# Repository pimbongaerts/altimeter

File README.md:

# Altimeter_v2

Intervalometer with serial interface based on Mega2560 MCU

*Current application:*

* Intervalometer for photogrammetry surveys (triggering a Canon 5DsR DSLR every second)
* Real-time sensor feedback underwater (through attached OLED display):
  * Levelling and altitude (through 2 x altimeters: [BlueRobotics Ping Sonar](https://bluerobotics.com/store/sensors-sonars-cameras/sonar/ping-sonar-r2-rp/))
  * Read-out USBL communications (through [BluePrint Subsea X150 USBL](https://www.blueprintsubsea.com/pages/product.php?PN=BP00795))
  * Depth and "bottom-depth" based on altitude (through [BlueRobotics Depth Sensor](https://bluerobotics.com/store/sensors-sonars-cameras/sensors/bar30-sensor-r1/))
  * Stopwatch & intervalometer count (triggered by Remora remote)
* Logging synchronized sensor data on SD card

*Features:*

* Real-time clock (RTC) for timekeeping
* SD-card reader to log sensor data
* 4-Channel Optocoupler to trigger camera(s)
* Step-down regulator to run board & DSLR camera off external battery (e.g. from dive propulsion vehicle)
* Supports I2C (3.3V or 5V logic), UART and RS232 sensors
* Connectors for remote controller & I2C or SPI display
* Headers to connect with [Robotdyn MCU-PRO Mega 2560 board](https://robotdyn.com/mcu-pro-mega-2560-atmega2560-16au-usb-ch340c-with-pinheaders-2-lines-pinheaders-pitch-0-1.html), which can be programmed using Arduino IDE
* Fits inside [BlueRobotics 2" watertight enclosure](https://bluerobotics.com/product-category/watertight-enclosures/) (see image below)

## Schematic

[PDF Schematic](altimeter_v2_schematic.pdf)

* Note: LP3966 on schematic replaced with [TL1963AKTTRG3](https://www.digikey.com/product-detail/en/texas-instruments/TL1963AKTTRG3/296-35958-1-ND/4135050) (has the same footprint)

## Arduino code

[Arduino code](altimeter_v2.ino) (some features are currently commented out)

## PCB Design

[KiCad PCB file](altimeter_v2.kicad_pcb) / [Bill of materials](altimeter_v2_bill.csv)

* Note: footprint of the [XC1195CT-ND Crystal](https://www.digikey.com/product-detail/en/ecs-inc/ECS-327-12-5-17X-TR/XC1195CT-ND/827659) turned out to be incorrect, but could easily remedied with direct bridge to RTC pin

## Underwater housing

Image shows board installed in a [BlueRobotics 2" watertight enclosure](https://bluerobotics.com/product-category/watertight-enclosures/), and with a 20x4 OLED display connected. On the left side, there are penetrators for an on/off switch, a [BlueRobotics Depth Sensor](https://bluerobotics.com/store/sensors-sonars-cameras/sensors/bar30-sensor-r1/), and 2 x [BlueRobotics Ping Sonar](https://bluerobotics.com/store/sensors-sonars-cameras/sonar/ping-sonar-r2-rp/) (although on the photo only one connected, hence the "error" on the top-right of the display). On the right side, there is an Ikelite connector to connect with the camera (power and trigger), another Ikelite connector for the 3-button remote (Remora), a penetrator for a cable connecting with the Dive-Xtras Piranha DPV battery, and a penetrator for the cable connecting with the [BluePrint Subsea X150 USBL](https://www.blueprintsubsea.com/pages/product.php?PN=BP00795).

## Final notes

Acknowledging John Atkins for all the design advice! Currently working on next iteration with SAMD51 integrated on the board (no external controller board required).

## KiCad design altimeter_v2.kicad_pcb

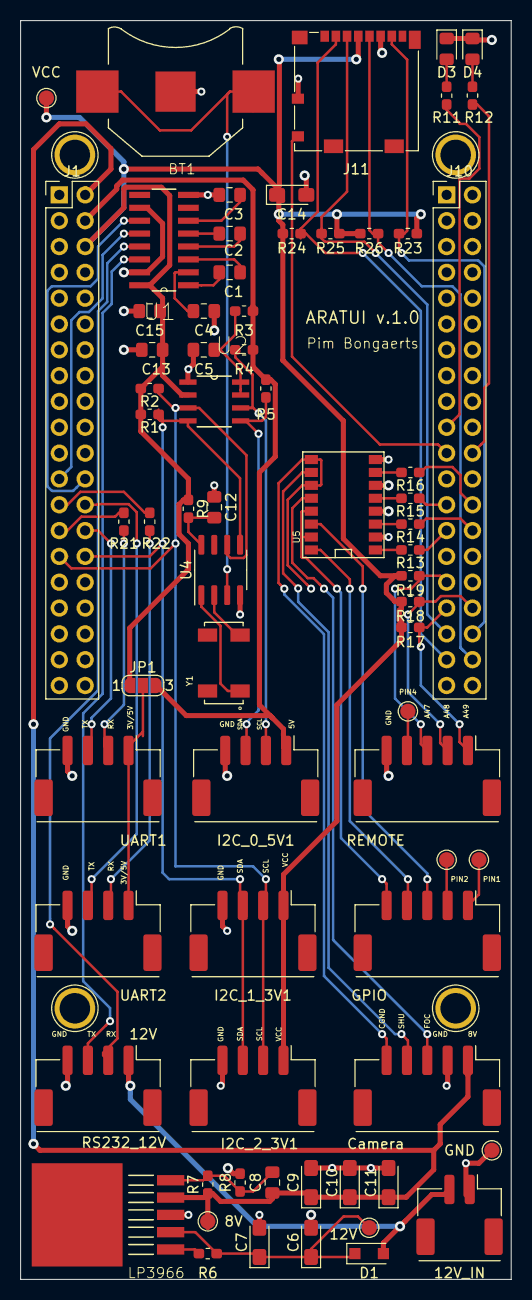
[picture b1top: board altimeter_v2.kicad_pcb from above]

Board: 2 copper layers, 48.3 x 123.8 mm, 70 parts (0 on the bottom side), 63 nets.

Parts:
8V, 12V: TestPoint; TestPoint_Pad_D1.5mm
12V_IN: 12V_IN; Molex_CLIK-Mate_502443-0270_1x02-1MP_P2.00mm_Vertical
BT1: BK-885; BAT_BK-885
C1, C2, C3, C4, C5, C12, C13, C15: 1uF; C_0805_2012Metric_Pad1.15x1.40mm_HandSolder
C6, C7, C9, C10, C11, C14: 33uF; CP_EIA-3216-10_Kemet-I_Pad1.58x1.35mm_HandSolder
C8: 68pF; C_0805_2012Metric_Pad1.15x1.40mm_HandSolder
Camera: Camera; Molex_CLIK-Mate_502443-0570_1x05-1MP_P2.00mm_Vertical
D1: D; D_SOD-123F
D3, D4: LED_Small; LED_0805_2012Metric_Pad1.15x1.40mm_HandSolder
GND: TestPoint; TestPoint_Pad_D1.5mm
GPIO: GPIO; Molex_CLIK-Mate_502443-0570_1x05-1MP_P2.00mm_Vertical
I2C_0_5V1: I2C_0_5V; Molex_CLIK-Mate_502443-0470_1x04-1MP_P2.00mm_Vertical
I2C_1_3V1: I2C_1_3V; Molex_CLIK-Mate_502443-0470_1x04-1MP_P2.00mm_Vertical
I2C_2_3V1: I2C_2_3V; Molex_CLIK-Mate_502443-0470_1x04-1MP_P2.00mm_Vertical
J1, J10: Conn_02x20_Odd_Even; PinHeader_2x20_P2.54mm_Vertical
J11: 5025700893; microSD_HC_Molex_104031-0811
JP1: SJ_Supply; SolderJumper-3_P1.3mm_Open_RoundedPad1.0x1.5mm_NumberLabels
LP3966: LP3966-ADJ_8.4V; TO170P1435X457-5N
PIN1, PIN2, PIN4: TestPoint; TestPoint_Pad_D1.5mm
R1, R2, R4, R5: 1.1K; R_0603_1608Metric_Pad1.05x0.95mm_HandSolder
R3: 200K; R_0603_1608Metric_Pad1.05x0.95mm_HandSolder
R6, R8, R9, R17, R18, R19, R21, R22, R23, R24, R25, R26: 11K; R_0603_1608Metric_Pad1.05x0.95mm_HandSolder
R7: 69K; R_0603_1608Metric_Pad1.05x0.95mm_HandSolder
R11, R12, R13, R14, R15, R16: 300; R_0603_1608Metric_Pad1.05x0.95mm_HandSolder
REMOTE: Remote; Molex_CLIK-Mate_502443-0570_1x05-1MP_P2.00mm_Vertical
RS232_12V: RS232; Molex_CLIK-Mate_502443-0470_1x04-1MP_P2.00mm_Vertical
U1: MAX3232CDR; SOIC127P600X175-16N
U2: PCA9306D; SOIC127P600X175-8N
U4: PCF8523T; SOIC-8_3.9x4.9mm_P1.27mm
U5: TCMT4100; SOP-16
UART1: UART_1; Molex_CLIK-Mate_502443-0470_1x04-1MP_P2.00mm_Vertical
UART2: UART_2; Molex_CLIK-Mate_502443-0470_1x04-1MP_P2.00mm_Vertical
VCC: TestPoint; TestPoint_Pad_D1.5mm
Y1: Crystal_Small; XTAL_ECS-.327-12.5-17X-TR

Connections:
+5V: I2C_0_5V1.1, J1.4, JP1.3, R3.1, R4.1, R5.1
+12V: 12V_IN.2, D1.2, RS232_12V.1
ARD35: J10.19, R11.2
ARD36: J10.22, R12.2
ARD37: J10.21, J11.10
ARD40: J10.26, R16.2
ARD41: J10.25, R15.2
ARD42: J10.28, R14.2
ARD43: J10.27, R13.2
ARD47: J10.31, R19.1, REMOTE.3
ARD48: J10.34, R18.1, REMOTE.2
ARD49: J10.33, R17.1, REMOTE.1
GND: 12V_IN.1, BT1.-, C3.1, C4.2, C5.2, C6.2, C7.2, C9.2, C10.2, C11.2, C12.1, C13.1, C14.2, C15.2, Camera.2, D3.1, D4.1, GND.1, I2C_0_5V1.4, I2C_1_3V1.4, I2C_2_3V1.4, J1.1, J1.7, J10.39, J10.40, J11.6, J11.9, LP3966.3, R8.2, REMOTE.5, RS232_12V.4, U1.8, U1.10, U1.15, U2.1, U4.4, U5.2, U5.4, U5.6, U5.8, UART1.4, UART2.4
MISO: J10.36, J11.7, R23.1
MOSI: J10.35, J11.3, R25.1
unnamed: BT1.S1+, BT1.S2+, U4.3
unnamed: C1.1, U1.1
unnamed: C1.2, U1.3
unnamed: C2.1, U1.4
unnamed: C2.2, U1.5
unnamed: C3.2, U1.6
unnamed: C4.1, U1.2
unnamed: C5.1, R3.2, U2.7, U2.8
unnamed: 12V.1, C6.1, C7.1, D1.1, LP3966.2, R6.2
unnamed: C8.2, LP3966.5, R7.2, R8.1
unnamed: C12.2, R9.2, U4.8
unnamed: Camera.3, U5.12
unnamed: Camera.4, U5.10
unnamed: Camera.5, U5.9, U5.11
unnamed: D3.2, R11.1
unnamed: D4.2, R12.1
unnamed: GPIO.1, PIN1.1
unnamed: GPIO.2, PIN2.1
unnamed: GPIO.3, U5.14
unnamed: GPIO.4, U5.16
unnamed: GPIO.5, U5.13, U5.15
unnamed: I2C_0_5V1.2, R4.2, U2.6
unnamed: I2C_0_5V1.3, R5.2, U2.5
unnamed: JP1.2, UART1.1, UART2.1
unnamed: LP3966.1, R6.1
unnamed: R13.1, U5.1
unnamed: R14.1, U5.3
unnamed: R15.1, U5.5
unnamed: R16.1, U5.7
unnamed: R21.2, UART1.2
unnamed: R22.2, UART2.2
unnamed: PIN4.1, REMOTE.4
unnamed: U4.1, Y1.1
unnamed: U4.2, Y1.2
RXD1: J1.27, R21.1
RXD2: J1.25, R22.1
RXD3: J1.23, U1.12
RX_RS232: RS232_12V.2, U1.13
SCK: J10.38, J11.5, R26.1
SCL: I2C_1_3V1.2, I2C_2_3V1.2, J1.29, R2.2, U2.3, U4.6
SDA: I2C_1_3V1.3, I2C_2_3V1.3, J1.30, R1.2, U2.4, U4.5
SS: J10.37, J11.2, R24.1
TXD1: J1.28, UART1.3
TXD2: J1.26, UART2.3
TXD3: J1.24, U1.11
TX_RS232: RS232_12V.3, U1.14
VCC: C13.2, C14.1, C15.1, I2C_1_3V1.1, I2C_2_3V1.1, J1.6, J11.4, JP1.1, R1.1, R2.1, R9.1, R17.2, R18.2, R19.2, R23.2, R24.2, R25.2, R26.2, U1.16, U2.2, VCC.1
VIN_8V: 8V.1, C8.1, C9.1, C10.1, C11.1, Camera.1, J1.2, LP3966.4, R7.1

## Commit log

2019-11-26 Added Arduino script
2020-05-14 Added files for Altimeter v2
2020-05-14 Added schematic image
2020-05-14 Added corrections
